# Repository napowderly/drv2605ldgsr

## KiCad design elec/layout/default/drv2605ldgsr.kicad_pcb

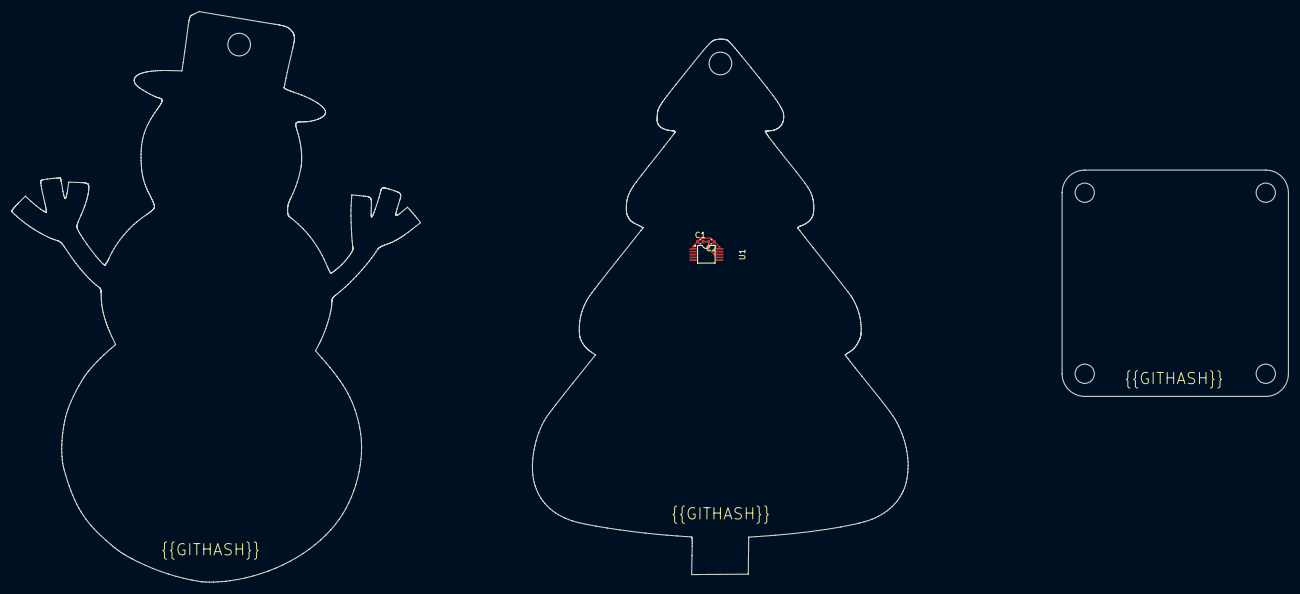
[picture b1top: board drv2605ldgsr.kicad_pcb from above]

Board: 2 copper layers, 66.4 x 94.6 mm, 3 parts (0 on the bottom side), 2 nets.

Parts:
C1, C2: Multilayer Ceramic Capacitors MLCC - SMD/SMT 1uF 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; C0402
U1: VSSOP-10_L3.0-W3.0-P0.50-LS4.9-BL

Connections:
gnd: C1.2, C2.2, U1.8
vcc: C1.1, C2.1, U1.1, U1.10

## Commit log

2024-02-17 Configure project
2024-02-17 layout
2024-02-17 cleanup
2024-03-08 Fix index lock issue
